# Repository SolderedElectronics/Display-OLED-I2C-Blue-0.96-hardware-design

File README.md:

# Display OLED I2C Blue 0.96" SSD1306 Hardware design

## About the product

|  |
| :----------------------------------------------------------: |
|      [Buy Display OLED I2C Blue 0.96" SSD1306](https://www.solde.red/333100)      |

Looking to add visuals to your Arduino projects? The I2C OLED breakout board is perfect for that. Because of its high contrast, you will be in awe of its crispness! The display is made from hundreds of LEDs, each representing one pixel in a 128x64 grid. Thus, it doesn't need any backlight, and it needs less power than the classic LCD screens. That’s 8192 pixels all individually lit at your fingertips!

The design is 5V ready with an onboard regulator, so is compatible with any 3.3V board. The breakout board uses only about 20 mA, depending on active pixels. It is easy to control over the I2C interface. It is even easier to connect with the easyC system - no soldering required!

## Repository contents

All Soldered Electronics hardware designed in KiCAD, and repositories are organized in the following way:

- CAD folder - contains KiCAD files (Schematics, Board, Panel Board), sorted by version. Change log lists all changes between versions.
- OUTPUTS - contains useful files, such as Bill of Materials (BOM), PDF of schematics, 3D .step file of the board and gerber files, sorted by version. 
- OUTPUTS -> Compliance - Certificates and useful legal stuff. 

## Want to contribute?

Please feel free to submit a pull request if you have any contributions. We encourage you to submit an issue or pull request if you find a bug. 

## About Soldered

At Soldered, we design and manufacture a wide selection of electronic products to help you turn your ideas into acts and bring you one step closer to your final project. Our products are intented for makers and crafted in-house by our experienced team in Osijek, Croatia. We believe that sharing is a crucial element for improvement and innovation, and we work hard to stay connected with all our makers regardless of their skill or experience level. Therefore, all our products are open-source. Finally, we always have your back. If you face any problem concerning either your shopping experience or your electronics project, our team will help you deal with it, offering efficient customer service and cost-free technical support anytime. Some of those might be useful for you:

- [Web Store](https://www.soldered.com/shop)
- [Tutorials & Projects](https://soldered.com/learn)
- [Community & Technical support](https://soldered.com/community)

## License info

All Soldered open-source hardware (OSH) is under The TAPR Open Hardware License. Read more in the LICENSE file. 

No warranty - all designs in this repository are distributed in the hope that they will be useful, but without any warranty. They are provided "AS IS", therefore without warranty of any kind, either expressed or implied. The entire quality and performance of what you do with the contents of this repository are your responsibility. In no event, Soldered Electronics will be liable for your damages, losses, including any general, special, incidental or consequential damage arising out of the use or inability to use the contents of this repository. 

## Have fun! 
And thank you from your fellow makers at Soldered Electronics.

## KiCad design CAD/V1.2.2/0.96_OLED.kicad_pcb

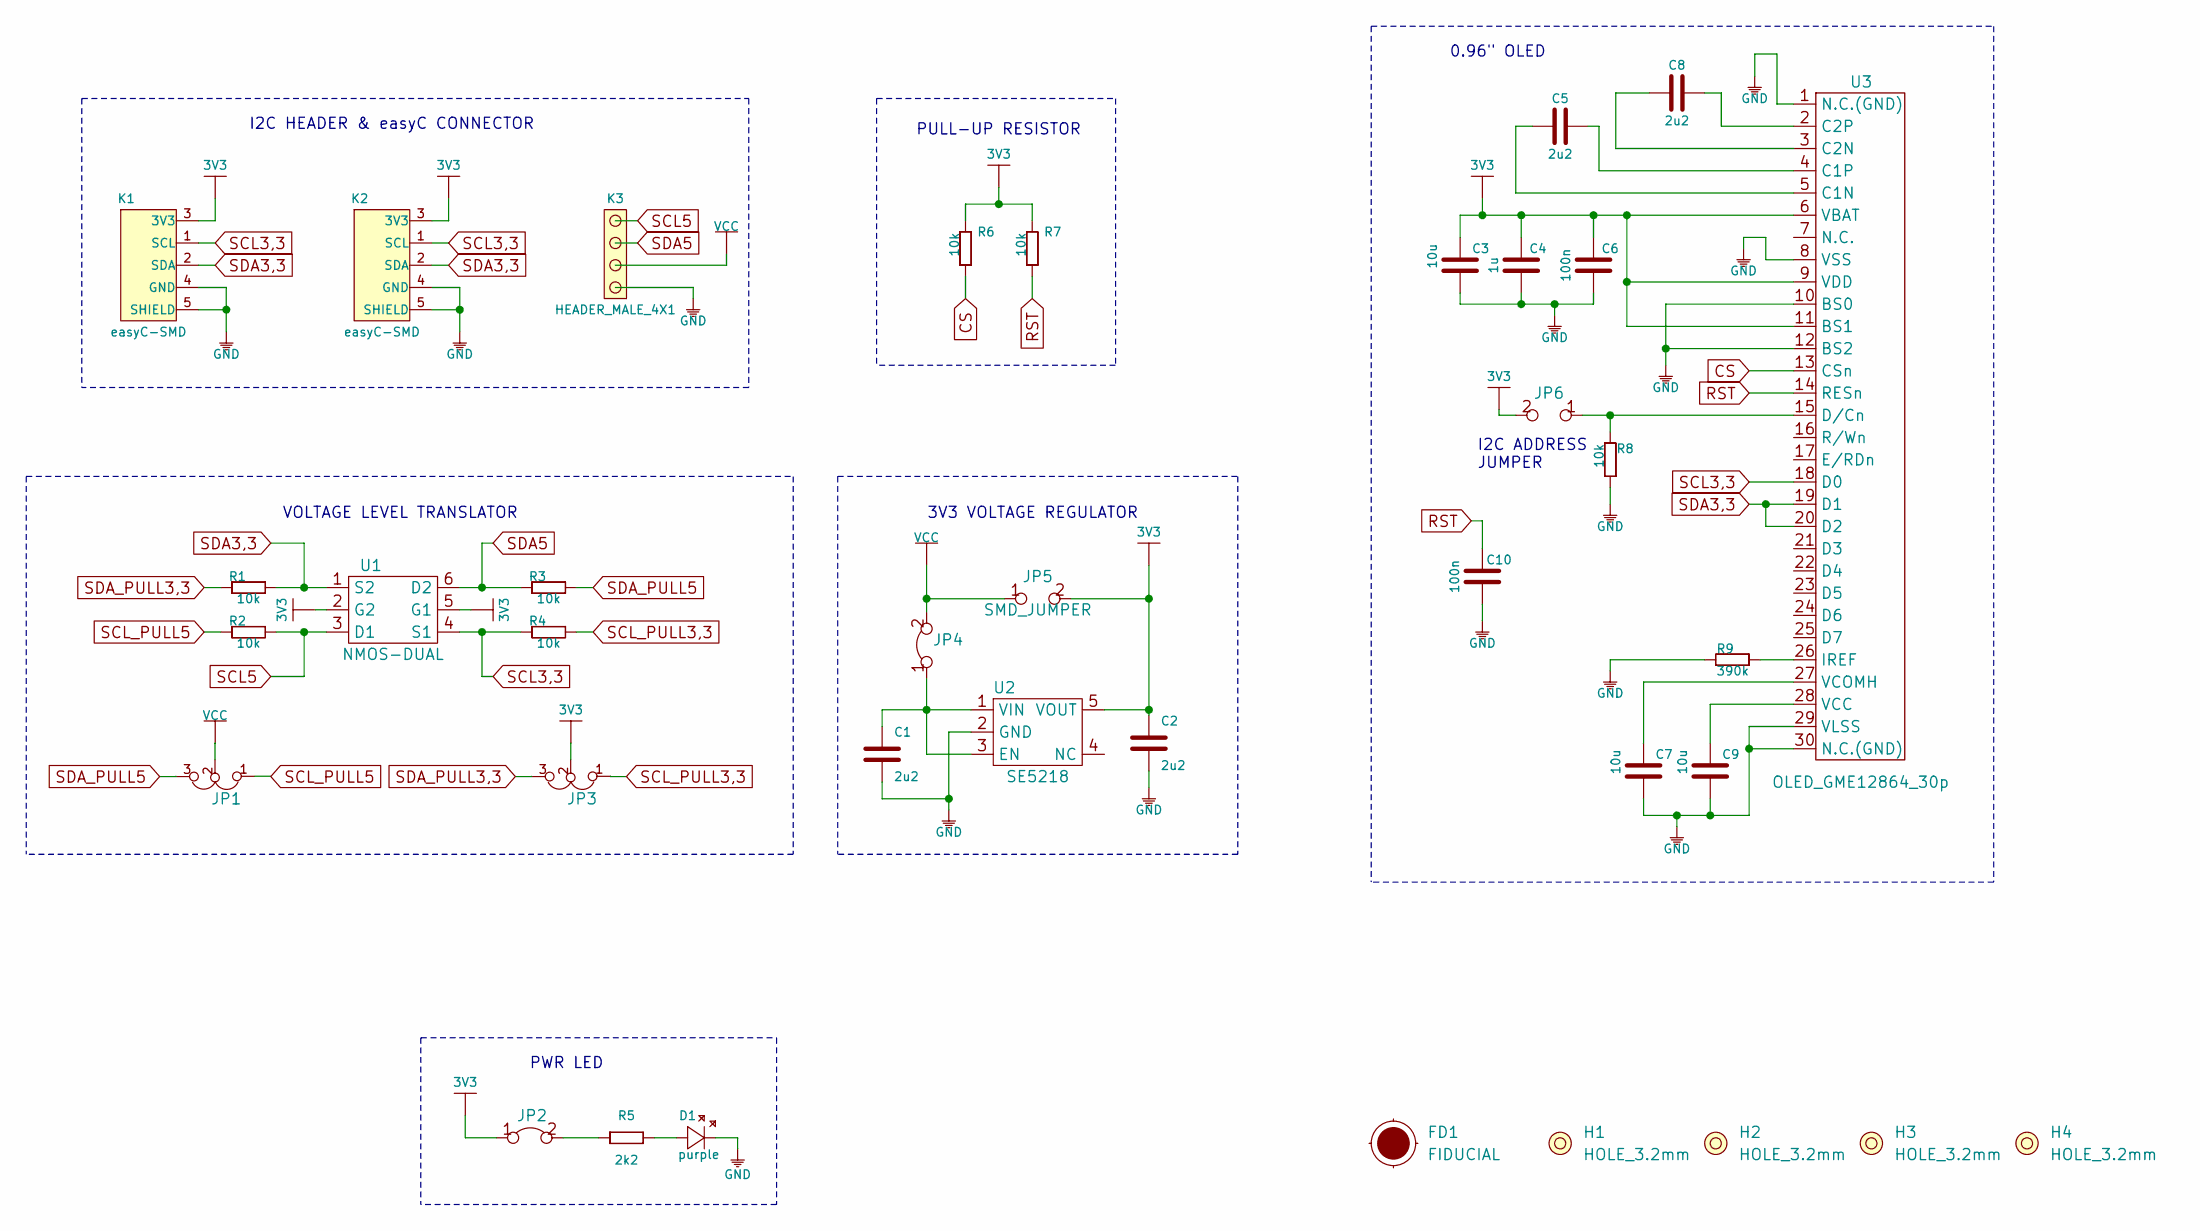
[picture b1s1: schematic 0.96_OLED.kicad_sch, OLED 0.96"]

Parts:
C1, C2, C5, C8: 2u2; 0603C
C3, C7, C9: 10u; 1206C
C4: 1u; 0603C
C6, C10: 100n; 0603C
D1: purple; 0402LED
FD1: FIDUCIAL; FIDUCIAL_23
H1, H2, H3, H4: HOLE_3.2mm
JP1, JP3: SMD_JUMPER_3_PAD_TRACE
JP2, JP4: SMD-JUMPER-CONNECTED_TRACE_SLODERMASK
JP5, JP6: SMD_JUMPER
K1, K2: easyC-SMD; easyC-connector
K3: HEADER_MALE_4X1
R1, R2, R3, R4, R6, R7, R8: 10k; 0603R
R5: 2k2; 0402R
R9: 390k; 0603R
U1: NMOS-DUAL; SOT-363
U2: SE5218; SOT-23-5
U3: OLED_GME12864_30p; OLED_GME128x64_30p

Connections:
3V3: C2.2, C3.1, C4.1, C6.1, JP2.1, JP3.2, JP5.2, JP6.2, K1.3 (3V3), K2.3 (3V3), R6.2, R7.2, U1.2 (G2), U1.5 (G1), U2.5 (VOUT), U3.6 (VBAT), U3.9 (VDD), U3.11 (BS1)
CS: R6.1, U3.13 (CSn)
GND: C1.1, C2.1, C3.2, C4.2, C6.2, C7.2, C9.2, C10.2, D1.2 (K), K1.4 (GND), K1.5 (SHIELD), K2.4 (GND), K2.5 (SHIELD), K3.1, R8.1, R9.2, U2.2 (GND), U3.1 (N.C.(GND)), U3.8 (VSS), U3.10 (BS0), U3.12 (BS2), U3.29 (VLSS), U3.30 (N.C.(GND))
unnamed: C1.2, JP4.1, U2.1 (VIN), U2.3 (EN)
unnamed: C5.1, U3.5 (C1N)
unnamed: C5.2, U3.4 (C1P)
unnamed: C7.1, U3.27 (VCOMH)
unnamed: C8.1, U3.3 (C2N)
unnamed: C8.2, U3.2 (C2P)
unnamed: C9.1, U3.28 (VCC)
unnamed: D1.1 (A), R5.2
unnamed: JP2.2, R5.1
unnamed: JP6.1, R8.2, U3.15 (D/Cn)
unnamed: R9.1, U3.26 (IREF)
RST: C10.1, R7.1, U3.14 (RESn)
SCL3,3: K1.1 (SCL), K2.1 (SCL), R4.1, U1.4 (S1), U3.18 (D0)
SCL5: K3.4, R2.2, U1.3 (D1)
SCL_PULL3,3: JP3.1, R4.2
SCL_PULL5: JP1.1, R2.1
SDA3,3: K1.2 (SDA), K2.2 (SDA), R1.2, U1.1 (S2), U3.19 (D1), U3.20 (D2)
SDA5: K3.3, R3.1, U1.6 (D2)
SDA_PULL3,3: JP3.3, R1.1
SDA_PULL5: JP1.3, R3.2
VCC: JP1.2, JP4.2, JP5.1, K3.2

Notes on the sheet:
0.96" OLED
3V3 VOLTAGE REGULATOR
I2C ADDRESS JUMPER
I2C HEADER & easyC CONNECTOR
PULL-UP RESISTOR
VOLTAGE LEVEL TRANSLATOR
PWR LED

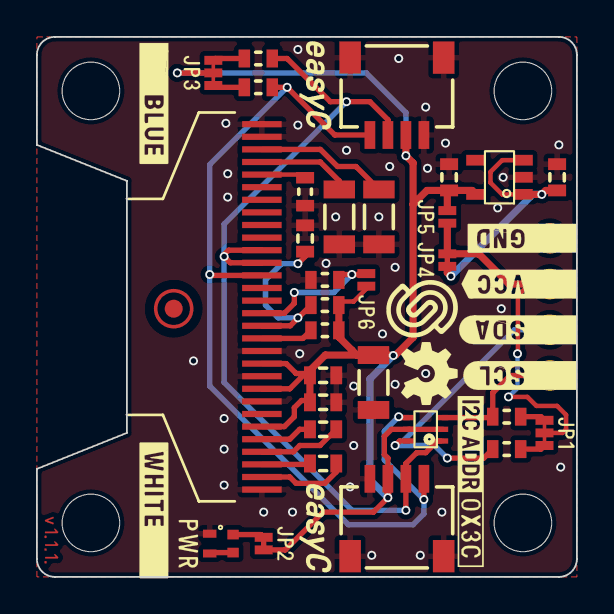
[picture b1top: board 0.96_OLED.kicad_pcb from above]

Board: 2 copper layers, 30.0 x 30.0 mm, 37 parts (0 on the bottom side), 24 nets.

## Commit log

2022-08-06 Updating open source files.
